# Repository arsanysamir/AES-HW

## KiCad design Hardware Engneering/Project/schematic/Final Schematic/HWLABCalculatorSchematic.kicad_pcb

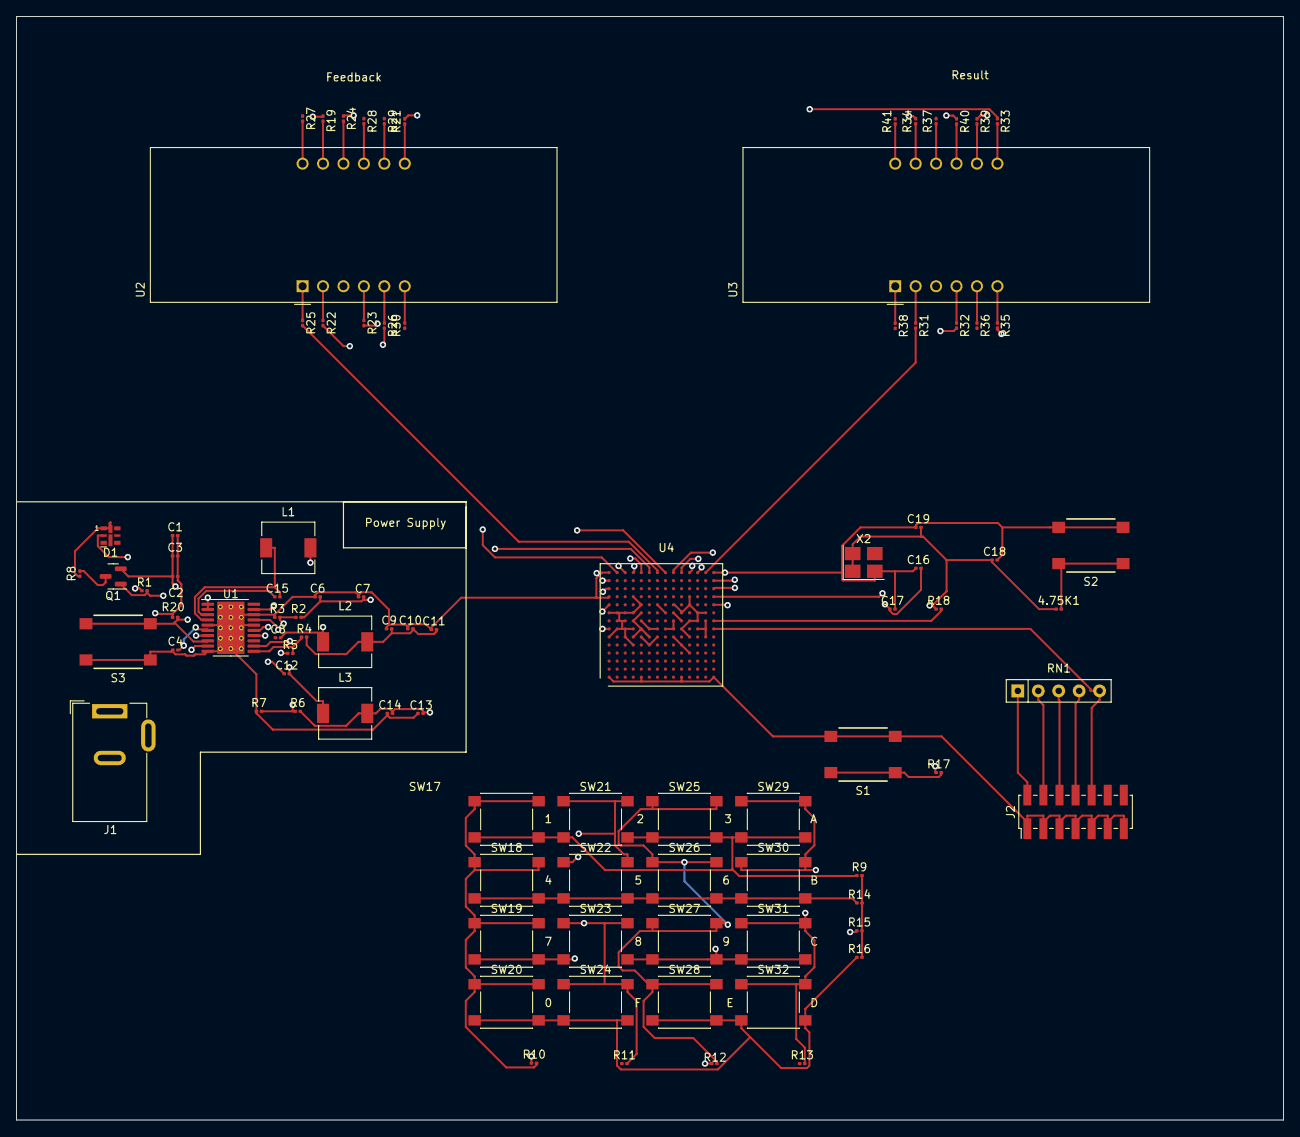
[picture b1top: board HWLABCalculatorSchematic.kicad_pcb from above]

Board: 4 copper layers, 157.5 x 137.2 mm, 92 parts (0 on the bottom side), 84 nets.

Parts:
4.75K1: R19; R_0201_0603Metric
C1, C2: 10 uF; C_0201_0603Metric
C3: 10uF; C_0201_0603Metric
C4: 1 uF; C_0201_0603Metric
C6, C7, C8, C9, C10, C11, C13, C14: 22 uF; C_0201_0603Metric
C12, C15: 0.1 uF; C_0201_0603Metric
C16: 0.1µF; C_0201_0603Metric
C17, C19: 0.1uF; C_0201_0603Metric
C18: 47uF; C_0201_0603Metric
D1: POWER_GOOD; LED-APA102-2020
J1: Barrel_Jack_Switch; BarrelJack_Wuerth_6941xx301002
J2: XILINX_JTAG; PinHeader_2x07_P2.00mm_Vertical_SMD
L1, L2, L3: 2.2 uH; L_6.3x6.3_H3
Q1: DMN2020L; SOT-23
R1, R20: 100K; R_0201_0603Metric
R2: 3.0K; R_0201_0603Metric
R3, R5, R7: 2.2K; R_0201_0603Metric
R4, R8: 680; R_0201_0603Metric
R6: 7.36K; R_0201_0603Metric
R9, R14, R15, R16: 10k; R_0201_0603Metric
R10, R11, R12, R13: 470; R_0201_0603Metric
R17, R18: 4.75k; R_0201_0603Metric
R19, R21, R22, R23, R24, R25, R26, R27, R28, R29, R30, R31, R32, R33, R34, R35, R36, R37, R38, R39, R40, R41: 330; R_0201_0603Metric
RN1: 10K; R_Array_SIP5
S1, S2, S3: B3FS_1010P
SW17, SW18, SW19, SW20, SW21, SW22, SW23, SW24, SW25, SW26, SW27, SW28, SW29, SW30, SW31, SW32: SW_Push; SW_Push_1P1T_NO_6x6mm_H9.5mm
U1: TPS65581; HTSSOP-20-1EP_4.4x6.5mm_P0.65mm_EP3.4x6.5mm_Mask2.75x3.43mm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
U2, U3: CC56-12CGKWA; CA56-12CGKWA
U4: XC7S50-FTGB196; Xilinx_FTGB196
X2: DSC61XX; Oscillator_SMD_Abracon_ASE-4Pin_3.2x2.5mm_HandSoldering

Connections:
+1V0: C9.2, C10.2, C11.2, L2.2, R4.2, U4.D6 (VCCINT), U4.D8 (VCCINT), U4.E7 (VCCINT), U4.E9 (VCCINT), U4.F6 (VCCINT), U4.G9 (VCCINT), U4.H6 (VCCINT), U4.J9 (VCCINT), U4.K6 (VCCINT), U4.K8 (VCCINT)
+1V8: C6.2, C7.2, C16.2, C17.1, L1.2, R2.2, U4.F8 (VCCADC_0), U4.H8 (VREFP_0)
+3.3V: 4.75K1.1, C13.2, C14.2, C18.1, C19.2, L3.2, R6.2, R17.1, R18.1, U4.M7 (M0_0), U4.N6 (VCCO_0), U4.N7 (CFGBVS_0), U4.N8 (VCCO_0), X2.1 (OE), X2.4 (VCC)
+3V3: D1.2 (A), J2.2 (VREF), R1.1, RN1.1 (common)
+12V: C1.2, C2.2, C3.2, J1.1, R20.1, U1.1 (VIN), U1.2 (VIN)
/FPGA JTGA Interface/INIT_B: R18.2, U4.P8 (INIT_B_0)
/FPGA JTGA Interface/JTAG_DO: J2.8 (TDO), RN1.4 (R3)
/FPGA JTGA Interface/JTAG_TCK: J2.6 (TCK), RN1.3 (R2), U4.A7 (TCK_0)
/FPGA JTGA Interface/JTAG_TDI: J2.10 (TDI), RN1.5 (R4), U4.P7 (TDI_0)
/FPGA JTGA Interface/JTAG_TMS: J2.4 (TMS), RN1.2 (R1), U4.M6 (TMS_0)
/FPGA JTGA Interface/PROGRAM_B: R17.2, S1.1, S1.2, U4.L7 (PROGRAM_B_0)
/power/PGOOD: Q1.1 (G), R1.2, U1.7 (PG)
/power/SW1: C15.2, L1.1, U1.4 (SW1)
/power/SW2: C8.2, L2.1, U1.19 (SW2)
/power/SW3: C12.2, L3.1, U1.15 (SW3)
COL1: R10.1, U4.A10 (IO_L3N_T0_DQS_EMCCLK_14)
COL2: R11.1, U4.B10 (IO_L3P_T0_DQS_PUDC_B_14)
COL3: R12.1, U4.A12 (IO_L4P_T0_D04_14)
COL4: R13.1, U4.C12 (IO_L6N_T0_D08_VREF_14)
GND: C1.1, C2.1, C3.1, C4.1, C6.1, C7.1, C9.1, C10.1, C11.1, C13.1, C14.1, C16.1, C17.2, C18.2, C19.1, J1.2, J2.1 (GND), J2.3 (GND), J2.5 (GND), J2.7 (GND), J2.9 (GND), J2.11 (GND), J2.13 (GND), Q1.2 (S), R3.1, R5.1, R7.1, S1.3, S1.4, S2.3, S2.4, S3.1, S3.2, U1.5 (PGND1), U1.10 (GND), U1.16 (PGND3), U1.18 (PGND2), U1.21 (PAD), U4.A1 (GND), U4.A6 (GND), U4.A9 (GND), U4.A11 (GND), U4.A14 (GND), U4.B4 (GND), U4.B7 (GND), U4.B8 (VCCBATT_0), U4.B9 (GND), U4.C2 (GND), U4.C6 (GND), U4.C7 (GND), U4.C8 (GND), U4.C9 (GND), U4.C13 (GND), U4.D5 (GND), U4.D7 (GND), U4.D9 (GND), U4.D11 (GND), U4.E1 (GND), U4.E3 (GND), U4.E6 (GND), U4.E8 (GND), U4.E10 (GND), U4.E14 (GND), U4.F5 (GND), U4.F7 (GNDADC_0), U4.F9 (GND), U4.G3 (GND), U4.G6 (GND), U4.G7 (VREFN_0), U4.G8 (VP_0), U4.G10 (GND), U4.G12 (GND), U4.H5 (GND), U4.H7 (VN_0), U4.H9 (GND), U4.J6 (GND), U4.J7 (DXN_0), U4.J8 (DXP_0), U4.J10 (GND), U4.K1 (GND), U4.K5 (GND), U4.K7 (GND), U4.K9 (GND), U4.K14 (GND), U4.L4 (GND), U4.L6 (GND), U4.L8 (GND), U4.L10 (GND), U4.L11 (GND), U4.M8 (M1_0), U4.M9 (M2_0), U4.N3 (GND), U4.N5 (GND), U4.N9 (GND), U4.N12 (GND), U4.P1 (GND), U4.P14 (GND), X2.2 (GND)
unnamed: D1.1 (K), R8.1
unnamed: Q1.3 (D), R8.2
unnamed: R10.2, SW17.1, SW18.1, SW19.1, SW20.1
unnamed: R11.2, SW21.1, SW22.1, SW23.1, SW24.1
unnamed: R12.2, SW25.1, SW26.1, SW27.1, SW28.1
unnamed: R13.2, SW29.1, SW30.1, SW31.1, SW32.1
unnamed: R20.2, S3.3, S3.4, U1.8 (EN1), U1.13 (EN3), U1.17 (EN2)
unnamed: C15.1, U1.3 (VBST1)
unnamed: C8.1, U1.20 (VBST2)
unnamed: C12.1, U1.14 (VBST3)
unnamed: R2.1, R3.2, U1.9 (VFB1)
unnamed: R4.1, R5.2, U1.11 (VFB2)
unnamed: R6.1, R7.2, U1.12 (VFB3)
unnamed: C4.2, U1.6 (VREG5)
unnamed: R27.2, U2.12 (CC1)
unnamed: R28.2, U2.9 (CC2)
unnamed: R29.2, U2.8 (CC3)
unnamed: R30.2, U2.6 (CC4)
unnamed: R19.1, U2.11 (a)
unnamed: R21.1, U2.7 (b)
unnamed: R23.1, U2.4 (c)
unnamed: R22.1, U2.2 (d)
unnamed: R25.1, U2.1 (e)
unnamed: R24.1, U2.10 (f)
unnamed: R26.1, U2.5 (g)
unnamed: R41.2, U3.12 (CC1)
unnamed: R40.2, U3.9 (CC2)
unnamed: R39.2, U3.8 (CC3)
unnamed: R35.2, U3.6 (CC4)
unnamed: R34.1, U3.11 (a)
unnamed: R33.1, U3.7 (b)
unnamed: R32.1, U3.4 (c)
unnamed: R31.1, U3.2 (d)
unnamed: R38.1, U3.1 (e)
unnamed: R37.1, U3.10 (f)
unnamed: R36.1, U3.5 (g)
ROW1: R9.1, SW17.2, SW21.2, SW25.2, SW29.2, U4.N10 (IO_L23P_T3_D19_14)
ROW2: R14.1, SW18.2, SW22.2, SW26.2, SW30.2, U4.N11 (IO_L23N_T3_D18_14)
ROW3: R15.1, SW19.2, SW23.2, SW27.2, SW31.2, U4.P10 (IO_L24P_T3_D17_14)
ROW4: R16.1, SW20.2, SW24.2, SW28.2, SW32.2, U4.M10 (IO_25_14)
SEG1A: R19.2, U4.B14 (IO_L5N_T0_D07_14)
SEG1B: R21.2, U4.C14 (IO_L11N_T1_SRCC_14)
SEG1C: R23.2, U4.D14 (IO_L11P_T1_SRCC_14)
SEG1CC1: R27.1, U4.B13 (IO_L5P_T0_D06_14)
SEG1CC2: R28.1, U4.D13 (IO_L8N_T1_D12_14)
SEG1CC3: R29.1, U4.E13 (IO_L10N_T1_D15_14)
SEG1CC4: R30.1, U4.F13 (IO_L10P_T1_D14_14)
SEG1D: R22.2, U4.F14 (IO_L9N_T1_DQS_D13_14)
SEG1E: R25.2, U4.G14 (IO_L9P_T1_DQS_14)
SEG1F: R24.2, U4.H14 (IO_L14N_T2_SRCC_14)
SEG1G: R26.2, U4.A13 (IO_L4N_T0_D05_14)
SEG2A: R34.2, U4.J14 (IO_L18N_T2_D27_14)
SEG2B: R33.2, U4.L14 (IO_L15N_T2_DQS_DOUT_CSO_B_14)
SEG2C: R32.2, U4.M14 (IO_L21N_T3_DQS_D22_14)
SEG2CC1: R41.1, U4.M13 (IO_L15P_T2_DQS_RDWR_B_14)
SEG2CC2: R40.1, U4.P13 (IO_L22N_T3_D20_14)
SEG2CC3: R39.1, U4.P12 (IO_L22P_T3_D21_14)
SEG2CC4: R35.1, U4.P11 (IO_L24N_T3_D16_14)
SEG2D: R31.2, U4.N14 (IO_L21P_T3_DQS_14)
SEG2E: R38.2, U4.H13 (IO_L14P_T2_SRCC_14)
SEG2F: R37.2, U4.J13 (IO_L18P_T2_D28_14)
SEG2G: R36.2, U4.L13 (IO_L16N_T2_D31_14)
SYSRES: 4.75K1.2, S2.1, S2.2
VCCKEY: R9.2, R14.2, R15.2, R16.2, U4.G13 (VCCO_14)

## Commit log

2023-04-20 Create de
2023-04-27 Create VHDL Code for Full adder
2023-04-27 Create VHDL Testbench Full Adder
2023-05-04 Create 4Bit Ripple Carry Adder
2023-05-04 Create 4Bit Ripple Carry Adder Testbench
2023-05-04 Create deleteme
2023-05-04 Create Half Adder VHDL Code
2023-05-04 Create Half Adder Testbench Code
2023-05-04 Create 4Bit Ripple Carry Adder VHDL Code
2023-05-11 Add files via upload
    1st arduino code without connection to broker (only for sensors)
2023-05-11 Create Half Adder Testbench
2023-05-11 Create Full Adder VHDL Code
2023-05-11 Create Full Adder Testbench
2023-05-11 Create 4 Bit Ripple Carry adder VHDL Code
2023-05-11 Create 4 Bit Ripple Carry adder Testbench
2023-05-11 Create 4 Bit Adder\Subtractor VHDL Code
2023-05-11 Create 4 Bit Adder\Subtractor Testbench
2023-05-30 Create 12switch12leds_Nexys-A7-100T-Master
2023-06-07 Implementation of the seven-segment display.
    Function: Print 0-9 with 1-second interval
2023-06-15 Create del
